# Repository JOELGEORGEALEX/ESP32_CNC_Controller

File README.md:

# ESP32_CNC_Controller_VERSION_1.0
## ESP32 based CNC controller board
* The idea is to build a ESP32 GRBL based CNC controller board
### Objectives
* To build a wireless CNC controller board, so that the machines will become system independent
* Support 4 axis motors,SD_CARD,Axis limits/TMC_SPI.
* Flash the espwroom32 module directly from USB with FTDI chip,without use of hardware buttons
* Upload gcodesfiles /send gcodes live to CNC machines with the help of any systems
* Correct the issues that will surely occur in version 1.
### Version 1 Board
* As always jumper wires hanging here and there,as part of errors & corrections. But efforts were not wasted. Finally one awkward looking working board :)

### Eagle schematic

### FTDI 232RL flash circuit for ESPWROOM32

### Firmware flashing $###########Successsssss

### Web interface for axis control,GCODE upload

### SDCARD file manager for File read

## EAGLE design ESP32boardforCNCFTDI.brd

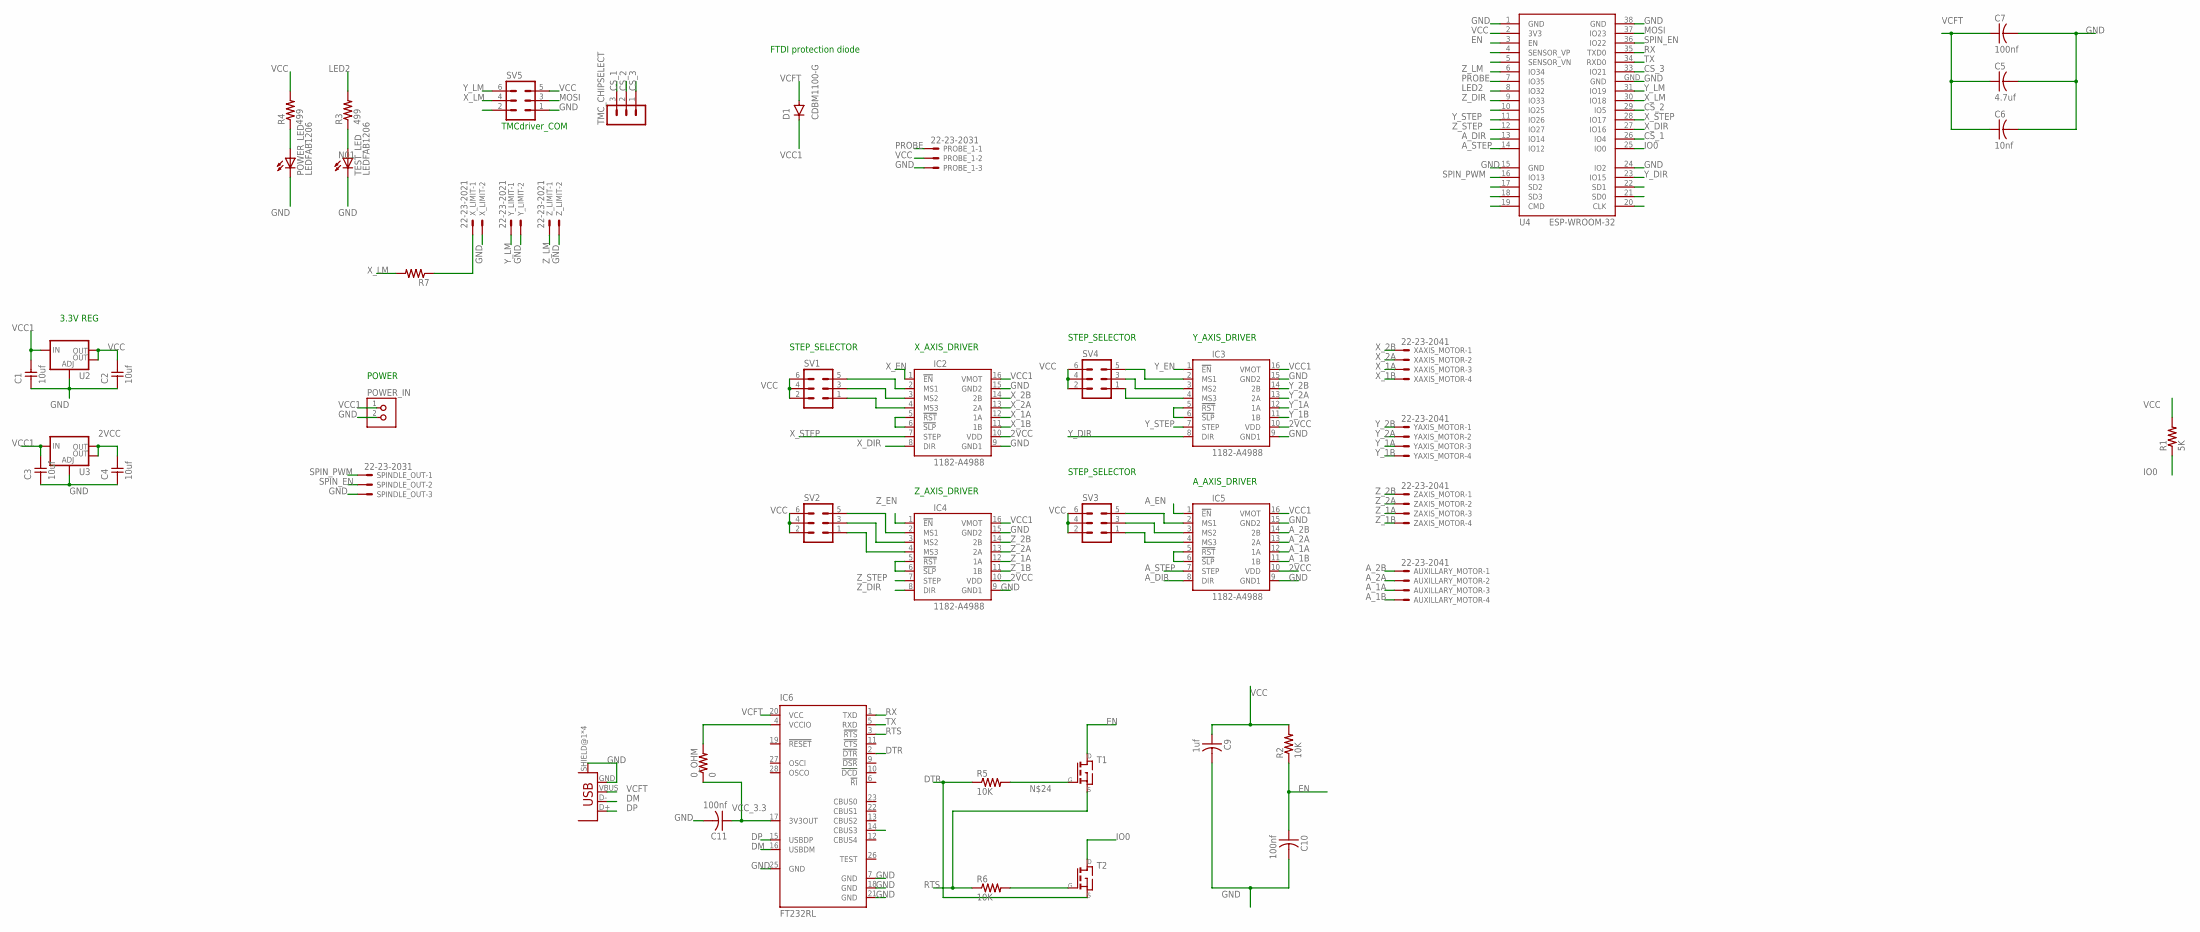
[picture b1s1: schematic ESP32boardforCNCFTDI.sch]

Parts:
0_OHM: 0; R1206FAB
AUXILLARY_MOTOR: 22-23-2041
C1, C2, C3, C4: 10uf; C1206FAB
C5: 4.7uf; C1206FAB
C6: 10nf; C1206FAB
C7, C10, C11: 100nf; C1206FAB
C9: 1uf; C1206FAB
D1: CDBM1100-G; MINI-SMA
IC2, IC3, IC4, IC5: 1182-A4988; A4988
IC6: FT232RL; SSOP28
POWER_IN: TERM-1X02-ADAFRUIT; 3.5MMTERM
POWER_LED: LEDFAB1206; LED1206FAB
PROBE_1: 22-23-2031
R1: 5K; R1206FAB
R2, R5, R6: 10K; R1206FAB
R3, R4: 499; R1206FAB
R7: RES-US1206FAB; R1206FAB
SPINDLE_OUT: 22-23-2031
SV1, SV2, SV3, SV4, SV5: MA03-2
T1, T2: NMOSFETSOT23; SOT-23
TEST_LED: LEDFAB1206; LED1206FAB
TMC_CHIPSELECT: MA03-1
U2, U3: V_REG_LM1117SOT223; SOT223
U4: ESP-WROOM-32
U$1: USB_MINIB
XAXIS_MOTOR: 22-23-2041
X_LIMIT: 22-23-2021
YAXIS_MOTOR: 22-23-2041
Y_LIMIT: 22-23-2021
ZAXIS_MOTOR: 22-23-2041
Z_LIMIT: 22-23-2021

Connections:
2VCC: C4.2, IC2.10 (VDD), IC3.10 (VDD), IC4.10 (VDD), IC5.10 (VDD), U3.2 (OUT), U3.4 (OUT)
A_1A: AUXILLARY_MOTOR.3, IC5.12 (1A)
A_1B: AUXILLARY_MOTOR.4, IC5.11 (1B)
A_2A: AUXILLARY_MOTOR.2, IC5.13 (2A)
A_2B: AUXILLARY_MOTOR.1, IC5.14 (2B)
A_DIR: IC5.8 (DIR), U4.13 (IO14)
A_EN: IC5.1 (!EN)
A_STEP: IC5.7 (STEP), U4.14 (IO12)
CS_1: TMC_CHIPSELECT.3, U4.26 (IO4)
CS_2: TMC_CHIPSELECT.2, U4.29 (IO5)
CS_3: TMC_CHIPSELECT.1, U4.33 (IO21)
DM: IC6.16 (USBDM), U$1.D-
DP: IC6.15 (USBDP), U$1.D+
DTR: IC6.2 (!DTR), R5.1, T2.2 (S)
EN: C10.1, R2.1, T1.1 (D), U4.3 (EN)
GND: C1.1, C2.1, C3.1, C4.1, C5.2, C6.2, C7.2, C9.2, C10.2, C11.2, IC2.9 (GND1), IC2.15 (GND2), IC3.9 (GND1), IC3.15 (GND2), IC4.9 (GND1), IC4.15 (GND2), IC5.9 (GND1), IC5.15 (GND2), IC6.7 (GND), IC6.18 (GND), IC6.21 (GND), IC6.25 (GND), POWER_IN.2, POWER_LED.2 (C), PROBE_1.3, SPINDLE_OUT.3, SV5.1, TEST_LED.2 (C), U2.1 (ADJ), U3.1 (ADJ), U4.1 (GND), U4.15 (GND), U4.24 (IO2), U4.38 (GND), U4.GND, U$1.GND, U$1.SHIELD@1 (SHIELD), U$1.SHIELD@2 (SHIELD), U$1.SHIELD@3 (SHIELD), U$1.SHIELD@4 (SHIELD), X_LIMIT.2, Y_LIMIT.2, Z_LIMIT.2
IO0: R1.1, T2.1 (D), U4.25 (IO0)
LED2: R3.2, U4.8 (IO32)
MOSI: SV5.3, U4.37 (IO23)
N01: R3.1, TEST_LED.1 (A)
unnamed: POWER_LED.1 (A), R4.1
unnamed: IC2.5 (!RST), IC2.6 (!SLP)
unnamed: IC3.5 (!RST), IC3.6 (!SLP)
unnamed: IC4.5 (!RST), IC4.6 (!SLP)
unnamed: IC5.5 (!RST), IC5.6 (!SLP)
unnamed: IC4.2 (MS1), SV2.5
unnamed: R7.1, X_LIMIT.1
unnamed: IC4.3 (MS2), SV2.3
unnamed: IC4.4 (MS3), SV2.1
unnamed: 0_OHM.2, IC6.4 (VCCIO)
unnamed: IC2.2 (MS1), SV1.5
unnamed: IC2.3 (MS2), SV1.3
unnamed: IC2.4 (MS3), SV1.1
unnamed: IC3.2 (MS1), SV4.5
unnamed: IC3.3 (MS2), SV4.3
unnamed: IC3.4 (MS3), SV4.1
unnamed: IC5.2 (MS1), SV3.5
unnamed: IC5.3 (MS2), SV3.3
unnamed: IC5.4 (MS3), SV3.1
unnamed: R5.2, T1.3 (G)
unnamed: R6.2, T2.3 (G)
PROBE: PROBE_1.1, U4.7 (IO35)
RTS: IC6.3 (!RTS), R6.1, T1.2 (S)
RX: IC6.1 (TXD), U4.35 (TXD0)
SPIN_EN: SPINDLE_OUT.2, U4.36 (IO22)
SPIN_PWM: SPINDLE_OUT.1, U4.16 (IO13)
TX: IC6.5 (RXD), U4.34 (RXD0)
VCC: C2.2, C9.1, PROBE_1.2, R1.2, R2.2, R4.2, SV1.2, SV1.4, SV1.6, SV2.2, SV2.4, SV2.6, SV3.2, SV3.4, SV3.6, SV4.2, SV4.4, SV4.6, SV5.5, U2.2 (OUT), U2.4 (OUT), U4.2 (3V3)
VCC1: C1.2, C3.2, D1.KATHODE, IC2.16 (VMOT), IC3.16 (VMOT), IC4.16 (VMOT), IC5.16 (VMOT), POWER_IN.1, U2.3 (IN), U3.3 (IN)
VCC_3.3: 0_OHM.1, C11.1, IC6.17 (3V3OUT)
VCFT: C5.1, C6.1, C7.1, D1.ANODE, IC6.20 (VCC), U$1.VBUS
X_1A: IC2.12 (1A), XAXIS_MOTOR.3
X_1B: IC2.11 (1B), XAXIS_MOTOR.4
X_2A: IC2.13 (2A), XAXIS_MOTOR.2
X_2B: IC2.14 (2B), XAXIS_MOTOR.1
X_DIR: IC2.8 (DIR), U4.27 (IO16)
X_EN: IC2.1 (!EN)
X_LM: R7.2, SV5.4, U4.30 (IO18)
X_STEP: IC2.7 (STEP), U4.28 (IO17)
Y_1A: IC3.12 (1A), YAXIS_MOTOR.3
Y_1B: IC3.11 (1B), YAXIS_MOTOR.4
Y_2A: IC3.13 (2A), YAXIS_MOTOR.2
Y_2B: IC3.14 (2B), YAXIS_MOTOR.1
Y_DIR: IC3.8 (DIR), U4.23 (IO15)
Y_EN: IC3.1 (!EN)
Y_LM: SV5.6, U4.31 (IO19), Y_LIMIT.1
Y_STEP: IC3.7 (STEP), U4.11 (IO26)
Z_1A: IC4.12 (1A), ZAXIS_MOTOR.3
Z_1B: IC4.11 (1B), ZAXIS_MOTOR.4
Z_2A: IC4.13 (2A), ZAXIS_MOTOR.2
Z_2B: IC4.14 (2B), ZAXIS_MOTOR.1
Z_DIR: IC4.8 (DIR), U4.9 (IO33)
Z_EN: IC4.1 (!EN)
Z_LM: U4.6 (IO34), Z_LIMIT.1
Z_STEP: IC4.7 (STEP), U4.12 (IO27)

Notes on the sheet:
FTDI protection diode
3.3V REG
POWER
X_AXIS_DRIVER
Y_AXIS_DRIVER
Z_AXIS_DRIVER
A_AXIS_DRIVER
STEP_SELECTOR
TMCdriver_COM

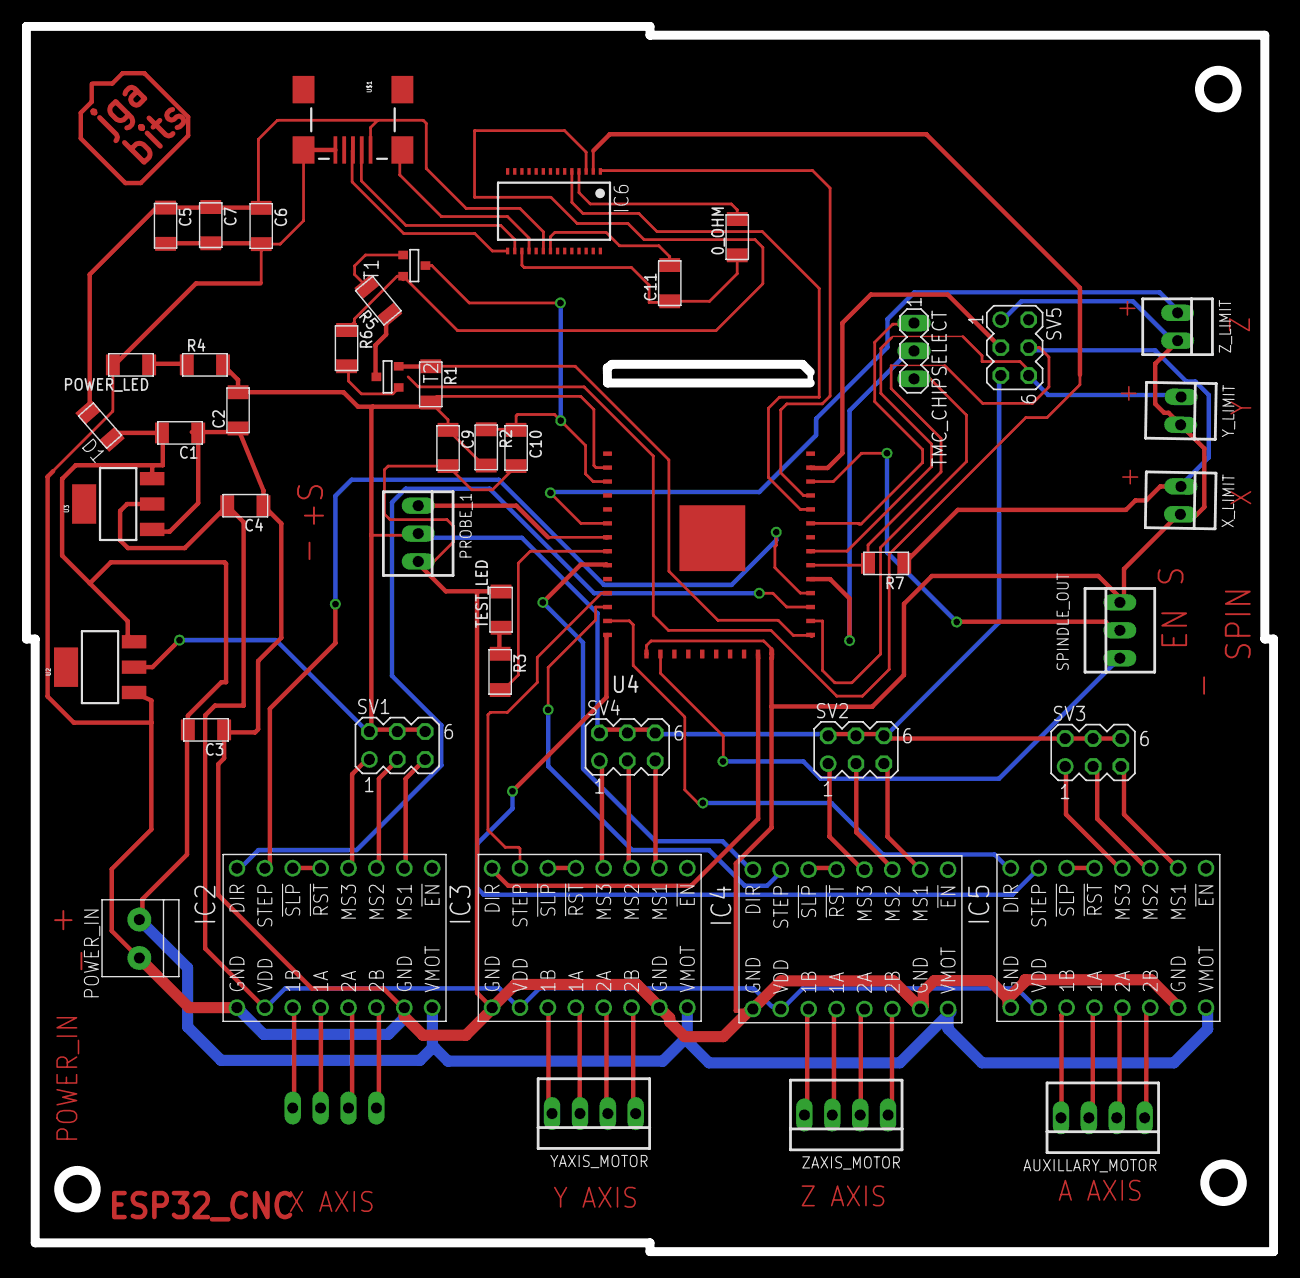
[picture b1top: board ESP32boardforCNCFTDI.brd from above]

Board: 2 copper layers, 113.6 x 111.6 mm, 48 parts (1 on the bottom side), 71 nets.

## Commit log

2021-12-14 Create eagle_file

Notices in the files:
parts and their libraries:
esp32: Creative Commons Attribution-ShareAlike 4.0 International
